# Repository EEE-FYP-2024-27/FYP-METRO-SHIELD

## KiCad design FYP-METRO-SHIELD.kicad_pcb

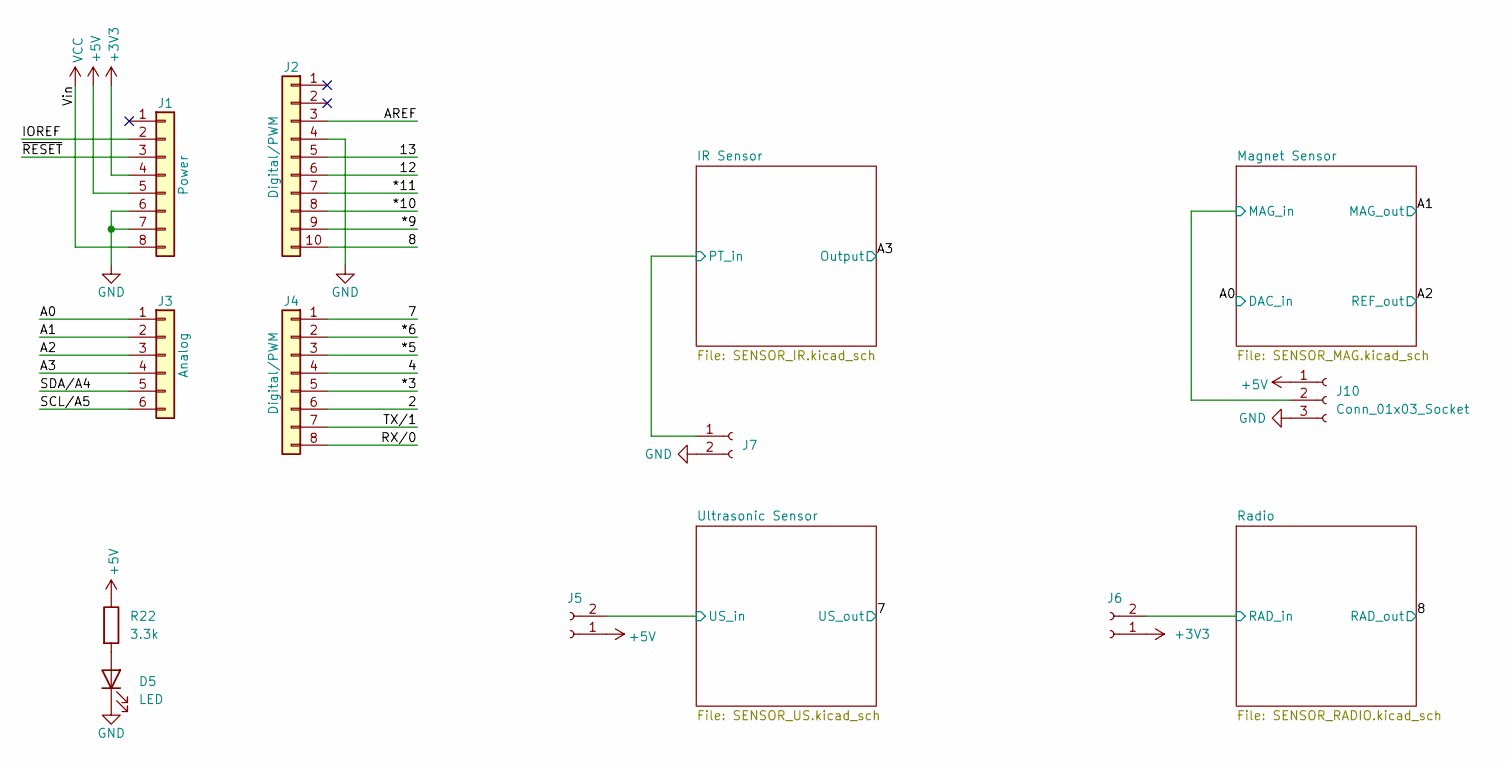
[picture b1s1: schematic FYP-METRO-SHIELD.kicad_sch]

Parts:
D5: LED; LED_D3.0mm
J1: Power; PinSocket_1x08_P2.54mm_Vertical
J2: Digital/PWM; PinSocket_1x10_P2.54mm_Vertical
J3: Analog; PinSocket_1x06_P2.54mm_Vertical
J4: Digital/PWM; PinSocket_1x08_P2.54mm_Vertical
J5, J6, J7: Conn_01x02_Socket; PinHeader_1x02_P2.54mm_Vertical
J10: Conn_01x03_Socket; PinHeader_1x03_P2.54mm_Vertical
R22: 3.3k; R_Axial_DIN0204_L3.6mm_D1.6mm_P5.08mm_Horizontal

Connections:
0.5V: J3.3; also elsewhere on the board
+3V3: J1.4, J6.1; also elsewhere on the board
+5V: J1.5, J5.1, J10.1, R22.1; also elsewhere on the board
/2: J4.6
/4: J4.4
/7: J4.1; also elsewhere on the board
/8: J2.10; also elsewhere on the board
/12: J2.6
/13: J2.5
/*3: J4.5
/*5: J4.3
/*6: J4.2
/*9: J2.9
/*10: J2.8
/*11: J2.7
/A0: J3.1; also elsewhere on the board
/A1: J3.2; also elsewhere on the board
/A3: J3.4; also elsewhere on the board
/AREF: J2.3
/IOREF: J1.2
/IR Sensor/PT_in: J7.1; also elsewhere on the board
/Magnet Sensor/MAG_in: J10.2; also elsewhere on the board
/RX/0: J4.8
/Radio/RAD_in: J6.2; also elsewhere on the board
/SCL/A5: J3.6
/SDA/A4: J3.5
/TX/1: J4.7
/Ultrasonic Sensor/US_in: J5.2; also elsewhere on the board
/~RESET: J1.3
GND: D5.1 (K), J1.6, J1.7, J2.4, J7.2, J10.3; also elsewhere on the board
unnamed: D5.2 (A), R22.2
VCC: J1.8

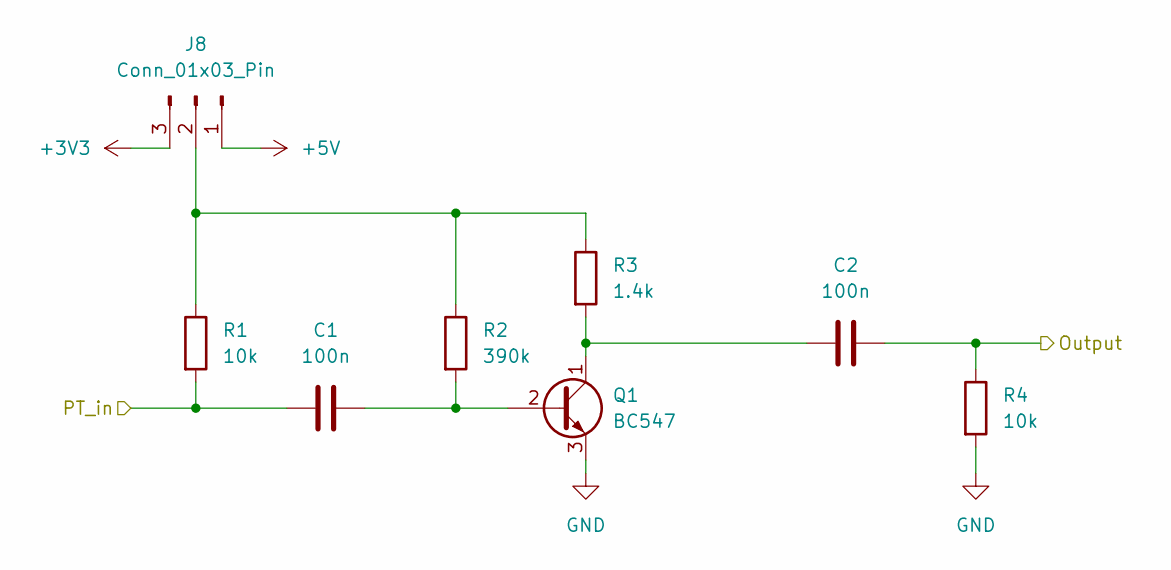
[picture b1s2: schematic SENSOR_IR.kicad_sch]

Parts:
C1, C2: 100n; C_Disc_D3.0mm_W2.0mm_P2.50mm
J8: Conn_01x03_Pin; PinHeader_1x03_P2.54mm_Vertical
Q1: BC547; TO-92_Inline
R1, R4: 10k; R_Axial_DIN0204_L3.6mm_D1.6mm_P5.08mm_Horizontal
R2: 390k; R_Axial_DIN0204_L3.6mm_D1.6mm_P5.08mm_Horizontal
R3: 1.4k; R_Axial_DIN0204_L3.6mm_D1.6mm_P5.08mm_Horizontal

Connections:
+3V3: J8.3; also elsewhere on the board
+5V: J8.1; also elsewhere on the board
/A3: C2.2, R4.1; also elsewhere on the board
/IR Sensor/PT_in: C1.1, R1.2; also elsewhere on the board
GND: Q1.3 (E), R4.2; also elsewhere on the board
unnamed: J8.2, R1.1, R2.1, R3.1
unnamed: C1.2, Q1.2 (B), R2.2
unnamed: C2.1, Q1.1 (C), R3.2

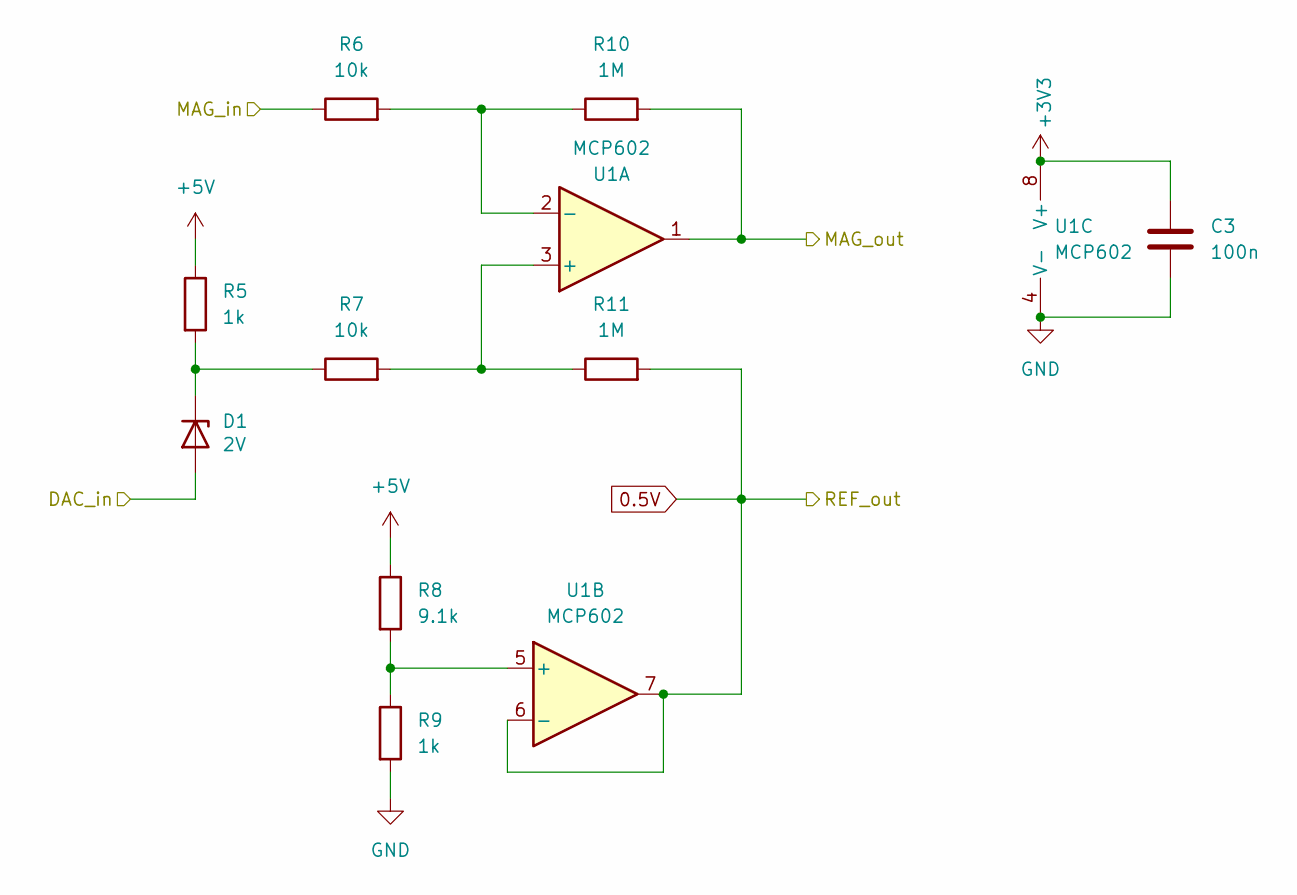
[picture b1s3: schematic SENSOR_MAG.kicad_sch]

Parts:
C3: 100n; C_Disc_D3.0mm_W2.0mm_P2.50mm
D1: BZT52C2V0-7-F; R_Axial_DIN0204_L3.6mm_D1.6mm_P5.08mm_Horizontal; Voltage 2V
R5, R9: 1k; R_Axial_DIN0204_L3.6mm_D1.6mm_P5.08mm_Horizontal
R6, R7: 10k; R_Axial_DIN0204_L3.6mm_D1.6mm_P5.08mm_Horizontal
R8: 9.1k; R_Axial_DIN0204_L3.6mm_D1.6mm_P5.08mm_Horizontal
R10, R11: 1M; R_Axial_DIN0204_L3.6mm_D1.6mm_P5.08mm_Horizontal
U1: MCP602; DIP-8_W7.62mm_Socket

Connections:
0.5V: R11.2, U1.6 (-), U1.7; also elsewhere on the board
+3V3: C3.1, U1.8 (V+); also elsewhere on the board
+5V: R5.1, R8.1; also elsewhere on the board
/A0: D1.2 (A); also elsewhere on the board
/A1: R10.2, U1.1; also elsewhere on the board
/Magnet Sensor/MAG_in: R6.1; also elsewhere on the board
GND: C3.2, R9.2, U1.4 (V-); also elsewhere on the board
unnamed: D1.1 (K), R5.2, R7.1
unnamed: R7.2, R11.1, U1.3 (+)
unnamed: R6.2, R10.1, U1.2 (-)
unnamed: R8.2, R9.1, U1.5 (+)

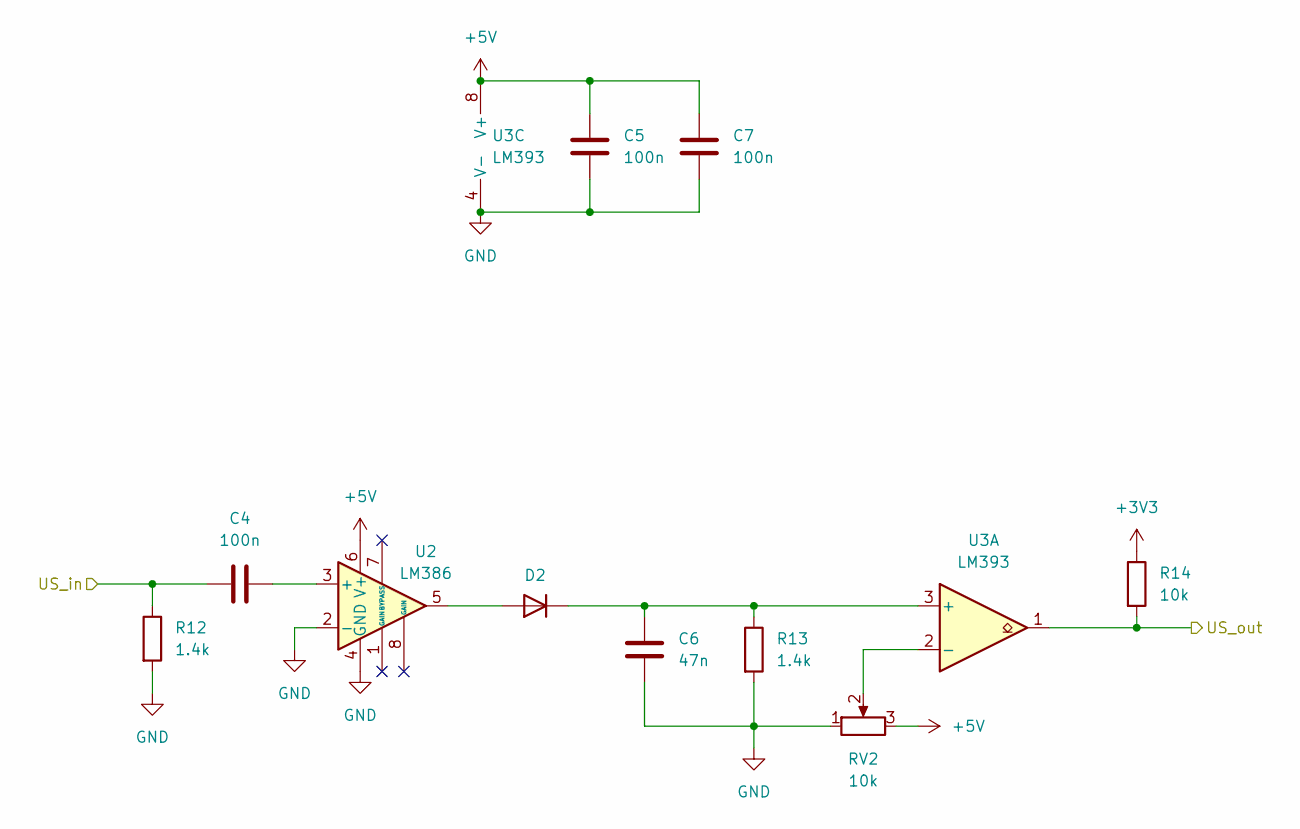
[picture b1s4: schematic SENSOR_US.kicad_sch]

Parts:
C4, C5, C7: 100n; C_Disc_D3.0mm_W2.0mm_P2.50mm
C6: 47n; C_Disc_D3.0mm_W2.0mm_P2.50mm
D2: D_DO-34_SOD68_P7.62mm_Horizontal
R12, R13: 1.4k; R_Axial_DIN0204_L3.6mm_D1.6mm_P5.08mm_Horizontal
R14: 10k; R_Axial_DIN0204_L3.6mm_D1.6mm_P5.08mm_Horizontal
RV2: 10k; Potentiometer_Bourns_3386F_Vertical
U2: LM386; DIP-8_W7.62mm_Socket
U3: LM393; DIP-8_W7.62mm_Socket

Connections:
+3V3: R14.1; also elsewhere on the board
+5V: C5.2, C7.2, RV2.3, U2.6 (V+), U3.8 (V+); also elsewhere on the board
/7: R14.2, U3.1; also elsewhere on the board
/Ultrasonic Sensor/US_in: C4.1, R12.1; also elsewhere on the board
GND: C5.1, C6.1, C7.1, R12.2, R13.2, RV2.1, U2.2 (-), U2.4 (GND), U3.4 (V-); also elsewhere on the board
unnamed: D2.2 (A), U2.5
unnamed: C6.2, D2.1 (K), R13.1, U3.3 (+)
unnamed: C4.2, U2.3 (+)
unnamed: RV2.2, U3.2 (-)

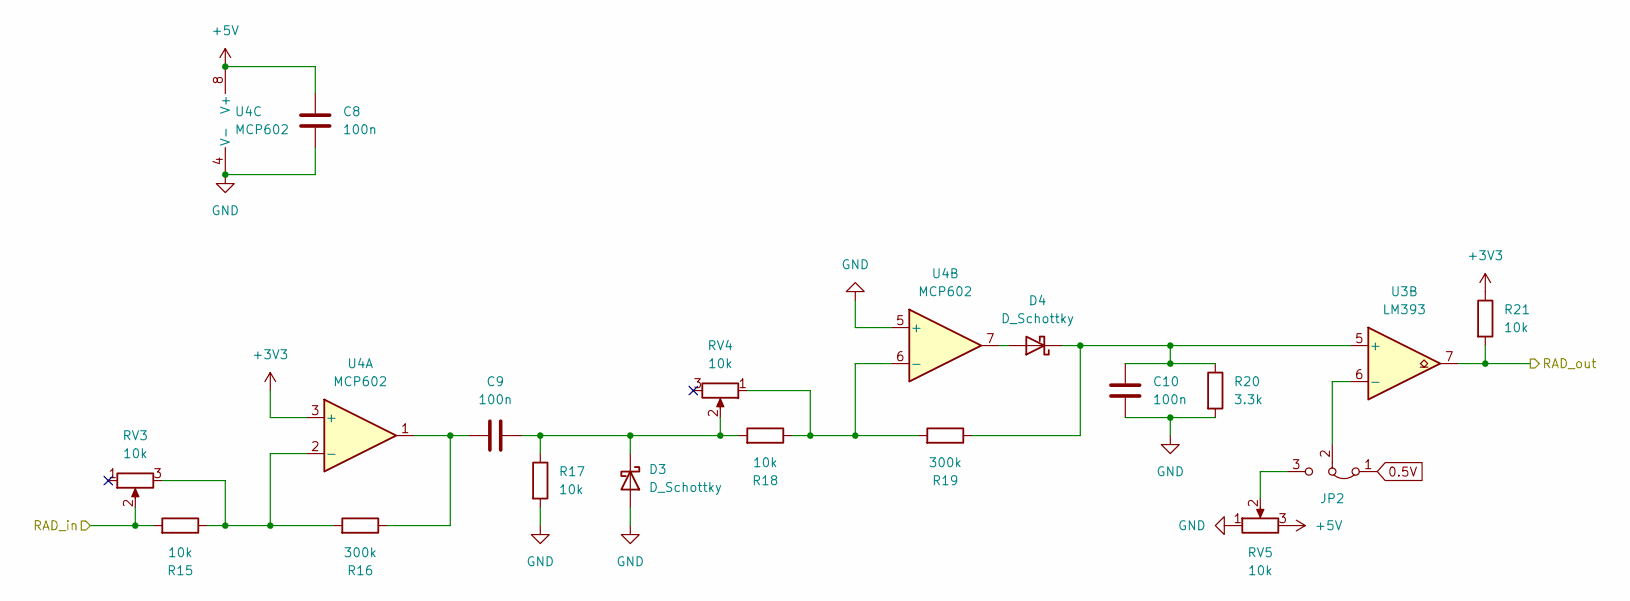
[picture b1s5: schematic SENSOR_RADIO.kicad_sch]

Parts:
C8, C9, C10: 100n; C_0805_2012Metric
D3, D4: D_Schottky; D_SOD-123
JP2: Jumper_3_Bridged12; SolderJumper-3_P1.3mm_Bridged12_RoundedPad1.0x1.5mm_NumberL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
R15, R17, R18, R21: 10k; R_0805_2012Metric
R16, R19: 300k; R_0805_2012Metric
R20: 3.3k; R_0805_2012Metric
RV3, RV4, RV5: 10k; Potentiometer_Bourns_TC33X_Vertical
U3: LM393; SOIC-8_3.9x4.9mm_P1.27mm
U4: MCP602; SOIC-8_3.9x4.9mm_P1.27mm

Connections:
+3V3: R21.1, U4.3 (+); also elsewhere on the board
+5V: C8.1, RV5.3, U4.8 (V+); also elsewhere on the board
/8: R21.2, U3.7; also elsewhere on the board
/Radio/RAD_in: R15.2, RV3.2; also elsewhere on the board
GND: C8.2, C10.1, D3.2 (A), R17.2, R20.2, RV5.1, U4.4 (V-), U4.5 (+); also elsewhere on the board
unnamed: C9.1, R16.1, U4.1
unnamed: C9.2, D3.1 (K), R17.1, R18.2, RV4.2
unnamed: D4.2 (A), U4.7
unnamed: C10.2, D4.1 (K), R19.1, R20.1, U3.5 (+)
unnamed 39: JP2.3 (B), RV5.2; also elsewhere on the board
unnamed 40: JP2.2 (C), U3.6 (-); also elsewhere on the board
unnamed: R15.1, R16.2, RV3.3, U4.2 (-)
unnamed: R18.1, R19.2, RV4.1, U4.6 (-)

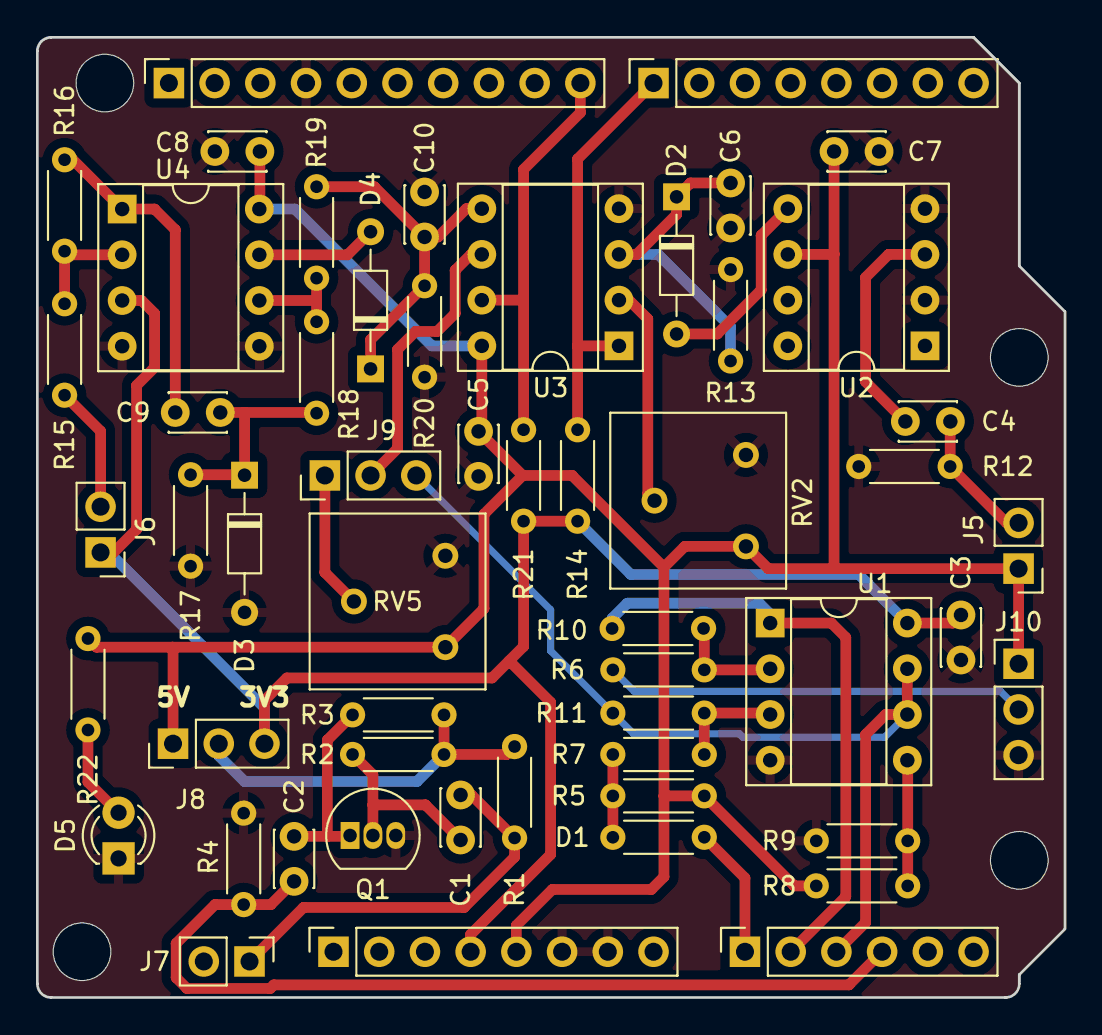
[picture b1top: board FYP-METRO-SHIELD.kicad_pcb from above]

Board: 2 copper layers, 57.1 x 53.3 mm, 58 parts (0 on the bottom side), 33 nets.

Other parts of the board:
J9: Conn_01x03_Pin; PinHeader_1x03_P2.54mm_Vertical
MH1, MH2, MH3, MH4: MountingHole_3.2mm

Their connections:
0.5V: J9.3; also elsewhere on the board
unnamed 39: J9.1; also elsewhere on the board
unnamed 40: J9.2; also elsewhere on the board
